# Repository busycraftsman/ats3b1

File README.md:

# ats3b1 project

# AT Sprint 3B.1
AT Sprint 3B1. 6 Bands HF CW/Digital Transceiver, designed by kd1jv.

# AT Sprint 3b.1 filter
filter board

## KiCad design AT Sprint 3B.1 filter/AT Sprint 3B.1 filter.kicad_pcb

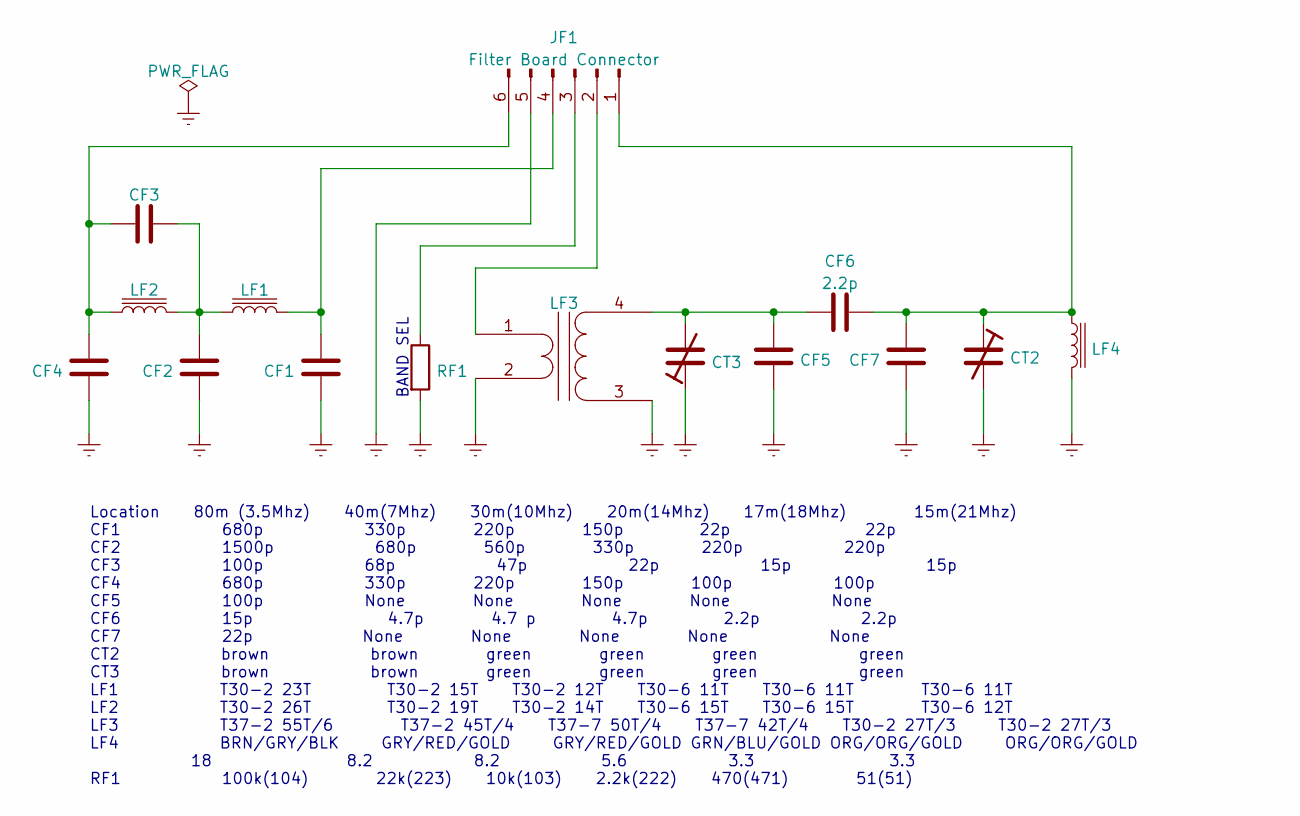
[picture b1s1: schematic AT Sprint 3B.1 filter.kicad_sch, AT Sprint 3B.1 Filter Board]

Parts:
CF1, CF2, CF3, CF4, CF5, CF7: C; C_Disc_D5.0mm_W2.5mm_P5.00mm
CF6: 2.2p; C_Disc_D5.0mm_W2.5mm_P5.00mm
CT2, CT3: C_Trim; C_TRIMMER_TZ03
JF1: Filter Board Connector; PinHeader_1x06_P2.54mm_Vertical
LF1, LF2: L_Iron; Toroid_horizontal_T37
LF3: Transformer_1P_1S_1vsN; Toroid_transformer_horizontal_T37
LF4: L_Iron; L_Axial_L7.0mm_D3.3mm_P2.54mm_Vertical_Fastron_MICC
RF1: R; R_0805_2012Metric_Pad1.20x1.40mm_HandSolder

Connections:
GNDREF: CF1.2, CF2.2, CF4.1, CF5.2, CF7.1, CT2.2, CT3.1, JF1.5, LF3.2 (AB), LF3.3 (SA), LF4.2, RF1.2
unnamed: CF1.1, JF1.4, LF1.2
unnamed: CF2.1, CF3.2, LF1.1, LF2.2
unnamed: CF3.1, CF4.2, JF1.6, LF2.1
unnamed: CF5.1, CF6.1, CT3.2, LF3.4 (SB)
unnamed: CF6.2, CF7.2, CT2.1, JF1.1, LF4.1
unnamed: JF1.2, LF3.1 (AA)
unnamed: JF1.3, RF1.1

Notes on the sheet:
BAND SEL
Location 80m (3.5Mhz) 40m(7Mhz) 30m(10Mhz) 20m(14Mhz) 17m(18Mhz) 15m(21Mhz) CF1 680p 330p 220p 150p 22p 22p CF2 1500p 680p 560p 330p 220p 220p CF3 100p 68p 47p 22p 15p 15p CF4 680p 330p 220p 150p 100p 100p CF5 100p None None None None None CF6 15p 4.7p 4.7 p 4.7p 2.2p 2.2p CF7 22p None None None No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

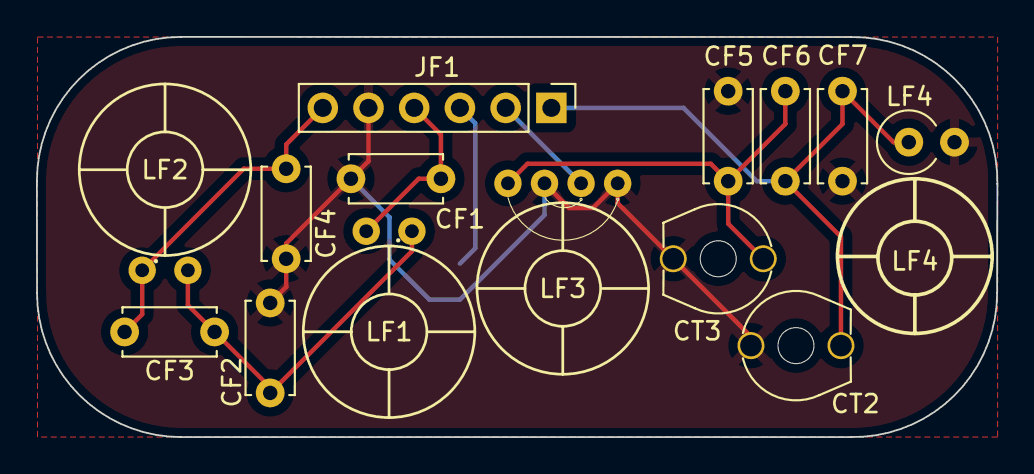
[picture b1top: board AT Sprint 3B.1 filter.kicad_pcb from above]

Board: 2 copper layers, 53.4 x 22.2 mm, 15 parts (1 on the bottom side), 8 nets.

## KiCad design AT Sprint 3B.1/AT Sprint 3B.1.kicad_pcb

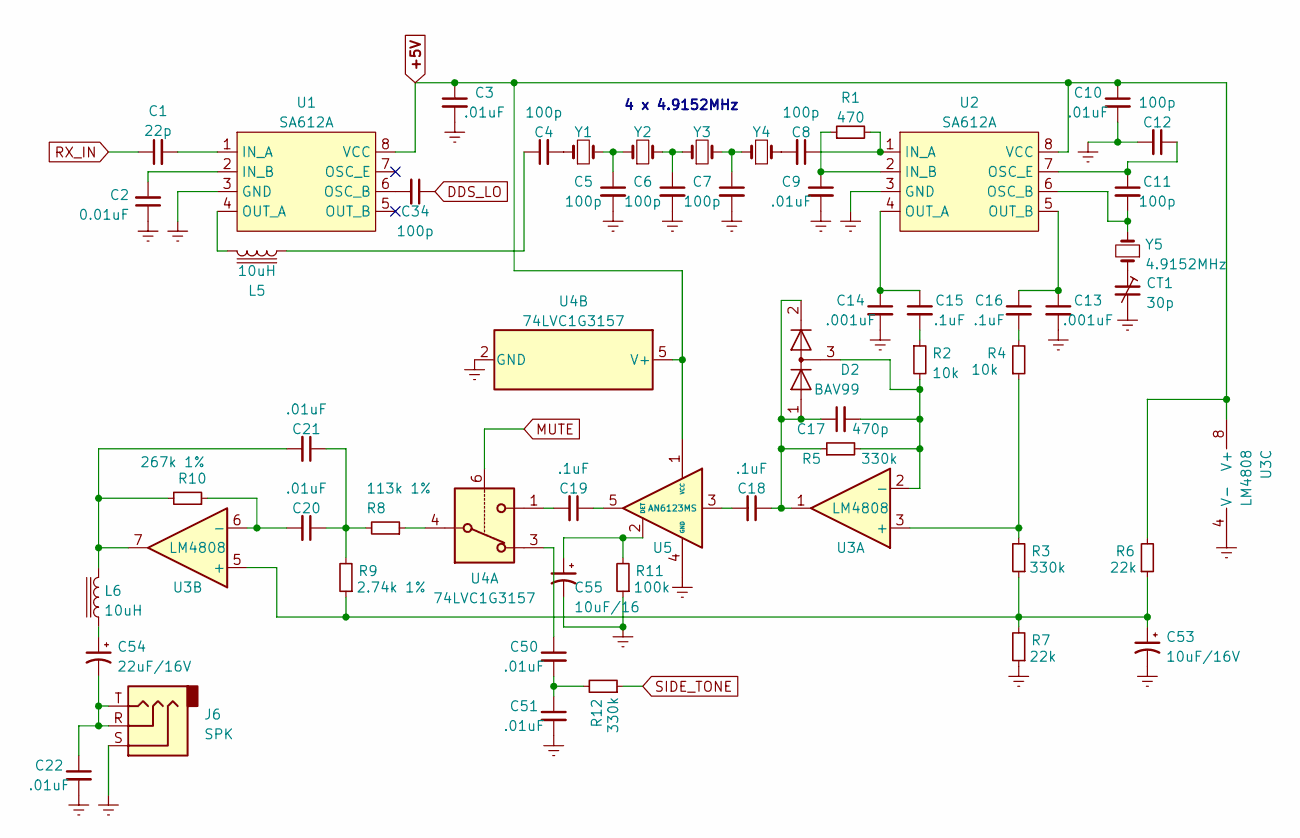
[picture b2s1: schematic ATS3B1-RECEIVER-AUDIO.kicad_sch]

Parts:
C1: 22p; C_0805_2012Metric
C2: 0.01uF; C_0805_2012Metric
C3, C9, C10, C20, C21, C22, C50, C51: .01uF; C_0805_2012Metric
C4, C5, C6, C7, C8, C11, C12, C34: 100p; C_0805_2012Metric
C13, C14: .001uF; C_0805_2012Metric
C15, C16, C18, C19: .1uF; C_0805_2012Metric
C17: 470p; C_0805_2012Metric
C53: 10uF/16V; CP_Radial_D5.0mm_P2.00mm
C54: 22uF/16V; CP_Radial_D5.0mm_P2.00mm
C55: 10uF/16; CP_Radial_D5.0mm_P2.00mm
CT1: 30p; C_TRIMMER_TZ03
D2: BAV99; SOT-23
J6: SPK; Jack_3.5mm_CUI_SJ-3523-SMT_Horizontal
L5, L6: 10uH; L_2010_5025Metric
R1: 470; R_0805_2012Metric
R2, R4: 10k; R_0805_2012Metric
R3, R5, R12: 330k; R_0805_2012Metric
R6, R7: 22k; R_0805_2012Metric
R8: 113k 1%; R_0805_2012Metric
R9: 2.74k 1%; R_0805_2012Metric
R10: 267k 1%; R_0805_2012Metric
R11: 100k; R_0805_2012Metric
U1, U2: SA612A; PowerIntegrations_SO-8
U3: LM4808; SOIC-8_3.9x4.9mm_P1.27mm
U4: 74LVC1G3157; SOT-666
U5: AN6123MS; SOT-553
Y1, Y2, Y3, Y4, Y5: 4.9152MHz; HC49US

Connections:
+5V: C3.1, C10.1, R6.2, U1.8 (VCC), U2.8 (VCC), U3.8 (V+), U4.5 (V+), U5.1 (VCC); also elsewhere on the board
DDS_LO: C34.1; also elsewhere on the board
GNDREF: C2.1, C3.2, C5.2, C6.2, C7.2, C9.2, C10.2, C12.2, C13.2, C14.2, C22.2, C51.2, C53.2, C55.2, CT1.2, J6.S, R7.1, R11.1, U1.3 (GND), U2.3 (GND), U3.4 (V-), U4.2 (GND), U5.4 (GND); also elsewhere on the board
unnamed: C1.2, U1.1 (IN_A)
unnamed: C2.2, U1.2 (IN_B)
unnamed: C4.1, L5.1
unnamed: C4.2, Y1.1
unnamed: C5.1, Y1.2, Y2.1
unnamed: C6.1, Y2.2, Y3.1
unnamed: C7.1, Y3.2, Y4.1
unnamed: C8.1, R1.2, U2.1 (IN_A)
unnamed: C8.2, Y4.2
unnamed: C9.1, R1.1, U2.2 (IN_B)
unnamed: C11.1, C12.1, U2.7 (OSC_E)
unnamed: C11.2, U2.6 (OSC_B), Y5.2
unnamed: C13.1, C16.1, U2.5 (OUT_B)
unnamed: C14.1, C15.1, U2.4 (OUT_A)
unnamed: C15.2, R2.1
unnamed: C16.2, R4.2
unnamed: C17.1, C18.1, D2.1 (K), D2.2 (A), R5.1, U3.1
unnamed: C17.2, D2.3 (K), R2.2, R5.2, U3.2 (-)
unnamed: C18.2, U5.3
unnamed: C19.1, U5.5
unnamed: C19.2, U4.1
unnamed: C20.1, C21.1, R8.2, R9.2
unnamed: C20.2, R10.1, U3.6 (-)
unnamed: C21.2, L6.2, R10.2, U3.7
unnamed: C22.1, C54.2, J6.R, J6.T
unnamed: C34.2, U1.6 (OSC_B)
unnamed: C50.1, U4.3
unnamed: C50.2, C51.1, R12.2
unnamed: C53.1, R3.1, R6.1, R7.2, R9.1, U3.5 (+)
unnamed: C54.1, L6.1
unnamed: C55.1, R11.2, U5.2 (DET)
unnamed: CT1.1, Y5.1
unnamed: L5.2, U1.4 (OUT_A)
unnamed: R3.2, R4.1, U3.3 (+)
unnamed: R8.1, U4.4
RX_IN: C1.1; also elsewhere on the board
SIDE_TONE: R12.1; also elsewhere on the board

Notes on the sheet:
4 x 4.9152MHz

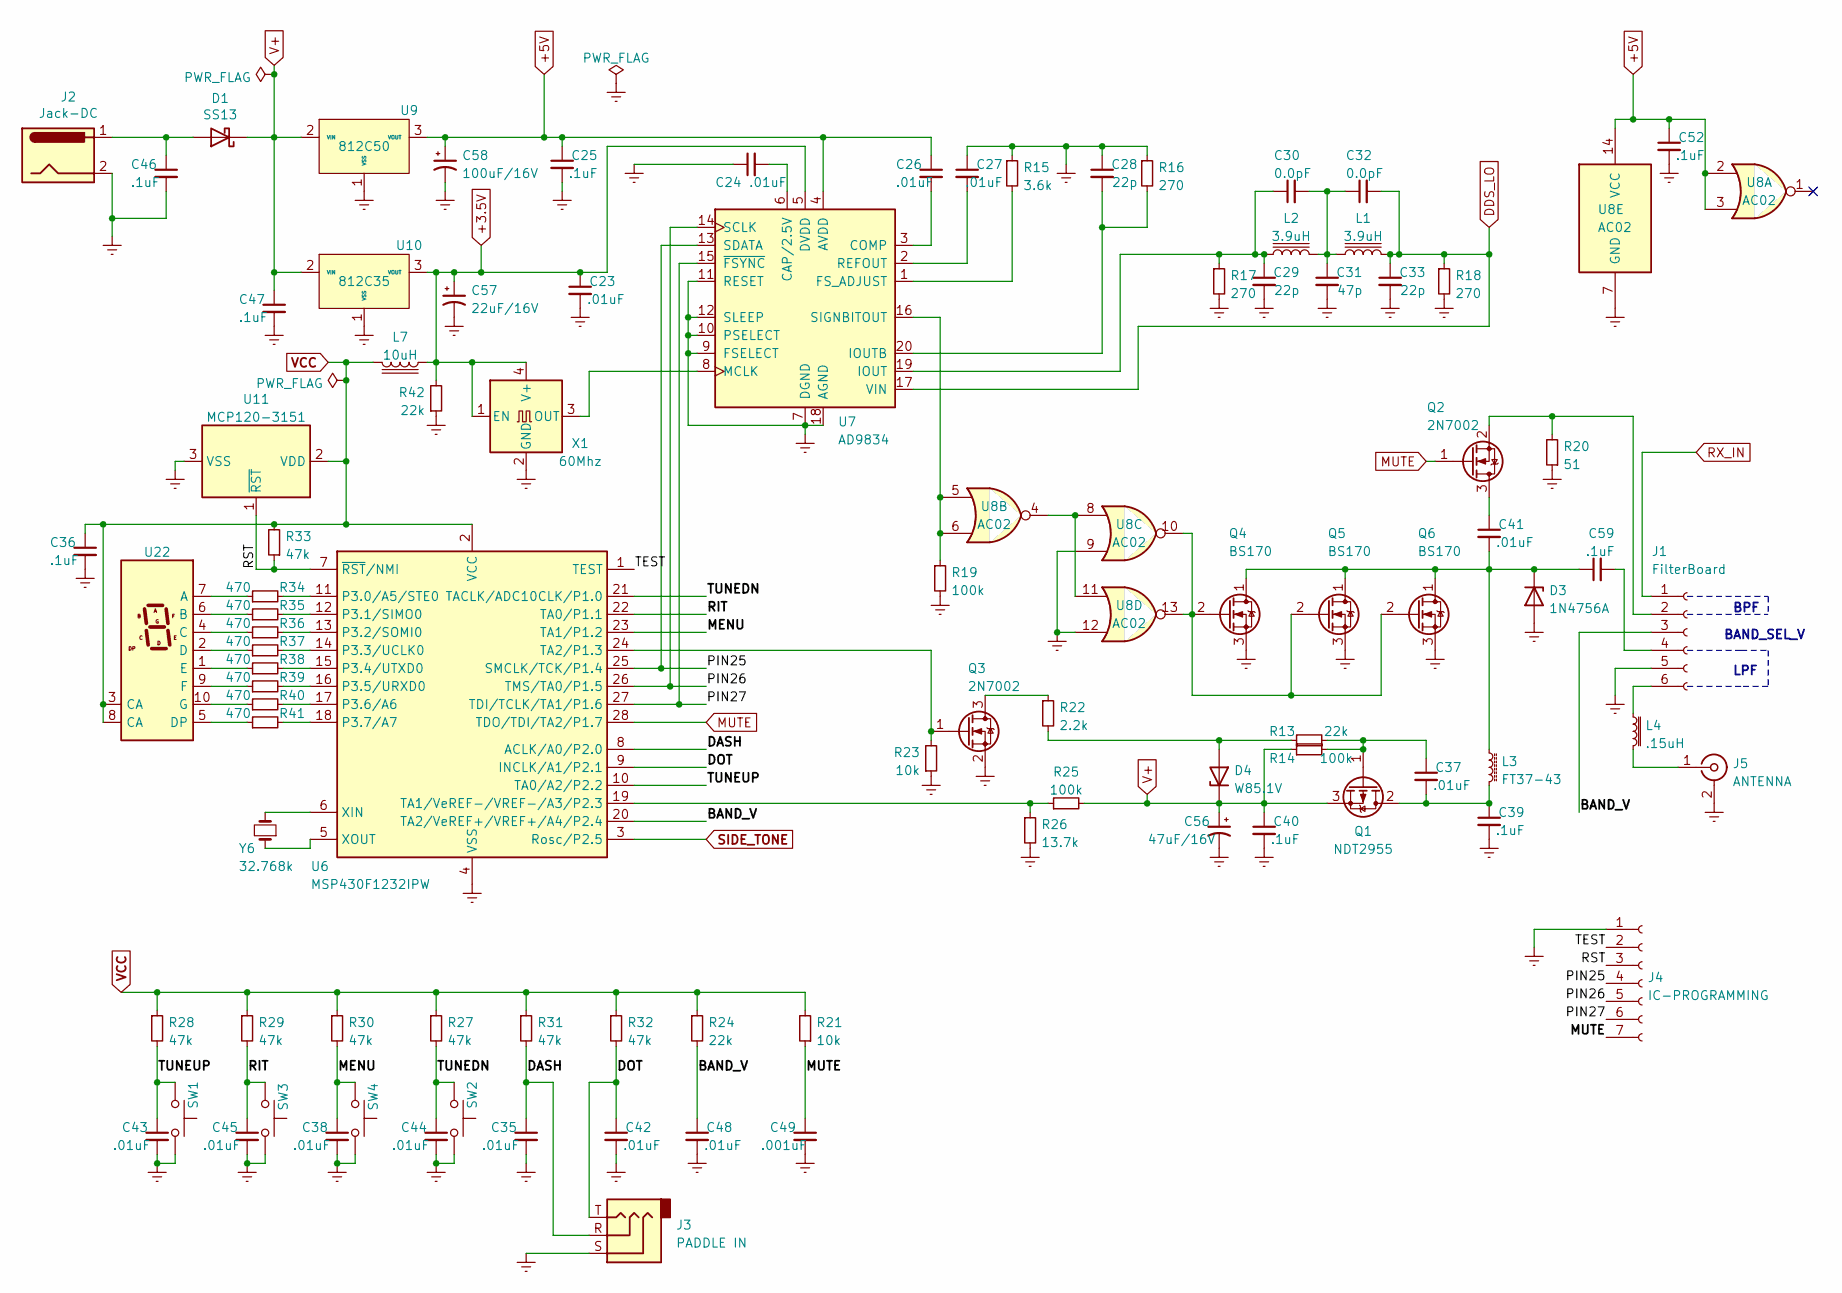
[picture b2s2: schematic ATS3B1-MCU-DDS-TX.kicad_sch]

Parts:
C23, C24, C26, C27, C35, C37, C38, C41, C42, C43, C44, C45, C48: .01uF; C_0805_2012Metric
C25, C36, C39, C40, C46, C47, C52: .1uF; C_0805_2012Metric
C28, C29, C33: 22p; C_0805_2012Metric
C30, C32: 0.0pF; C_0805_2012Metric
C31: 47p; C_0805_2012Metric
C49: .001uF; C_0805_2012Metric
C56: 47uF/16V; CP_Radial_D5.0mm_P2.00mm
C57: 22uF/16V; CP_Radial_D5.0mm_P2.00mm
C58: 100uF/16V; CP_Radial_D5.0mm_P2.00mm
C59: .1uF; C_Disc_D3.8mm_W2.6mm_P2.50mm
D1: SS13; D_SMA
D3: 1N4756A; D_DO-41_SOD81_P7.62mm_Horizontal
D4: W85.1V; D_SOD-123
J1: FilterBoard; PinSocket_1x06_P2.54mm_Vertical
J2: Jack-DC; CUI_PJ-041-SMT-TR
J3: PADDLE IN; Jack_3.5mm_CUI_SJ-3523-SMT_Horizontal
J4: IC-PROGRAMMING; PinHeader_1x07_P2.54mm_Vertical
J5: ANTENNA; PinHeader_1x02_P2.54mm_Vertical
L1, L2: 3.9uH; L_2010_5025Metric
L3: FT37-43; Choke_Toroid_horizontal_Diameter10-5mm_Amidon-FT37
L4: .15uH; L_2010_5025Metric
L7: 10uH; L_2010_5025Metric
Q1: NDT2955; Trans_SOT-223-4
Q2, Q3: 2N7002; SOT-23
Q4, Q5, Q6: BS170; TO-92
R13, R24, R42: 22k; R_0805_2012Metric
R14, R19, R25: 100k; R_0805_2012Metric
R15: 3.6k; R_0805_2012Metric
R16, R17, R18: 270; R_0805_2012Metric
R20: 51; R_0805_2012Metric
R21, R23: 10k; R_0805_2012Metric
R22: 2.2k; R_0805_2012Metric
R26: 13.7k; R_0805_2012Metric
R27, R28, R29, R30, R31, R32, R33: 47k; R_0805_2012Metric
R34, R35, R36, R37, R38, R39, R40, R41: 470; R_0805_2012Metric
SW1, SW2, SW3, SW4: SW_Push; SW_PUSH_6mm
U6: MSP430F1232IPW; TSSOP-28_4.4x9.7mm_P0.65mm
U7: AD9834; TSSOP-20_4.4x6.5mm_P0.65mm
U8: AC02; SSOP-14_5.3x6.2mm_P0.65mm
U9: 812C50; SOT-89-3
U10: 812C35; SOT-89-3
U11: MCP120-3151; SOT-23
U22: KCSA02-107; KCSC02-105
X1: 60Mhz; Oscillator_SMD_EuroQuartz_XO91-4Pin_7.0x5.0mm_HandSoldering
Y6: 32.768k; CRYSTAL-PTH-2X6-CYL

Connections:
+3.5V: C23.1, C57.1, L7.1, R42.2, U7.5 (DVDD), U10.3 (VOUT), X1.1 (EN), X1.4 (V+)
+5V: C25.1, C26.1, C52.1, C58.1, U7.4 (AVDD), U8.2, U8.3, U8.14 (VCC), U9.3 (VOUT); also elsewhere on the board
/ATS3B1-MCU-DDS-TX/BAND_V: C48.1, J1.3, R24.2, U6.20 (TA2/VeREF+/VREF+/A4/P2.4)
/ATS3B1-MCU-DDS-TX/DASH: C35.1, J3.R, R31.2, U6.8 (ACLK/A0/P2.0)
/ATS3B1-MCU-DDS-TX/DOT: C42.1, J3.T, R32.2, U6.9 (INCLK/A1/P2.1)
/ATS3B1-MCU-DDS-TX/MENU: C38.1, R30.2, SW4.2, U6.23 (TA1/P1.2)
/ATS3B1-MCU-DDS-TX/PIN25: J4.4, U6.25 (SMCLK/TCK/P1.4), U7.13 (SDATA)
/ATS3B1-MCU-DDS-TX/PIN26: J4.5, U6.26 (TMS/TA0/P1.5), U7.14 (SCLK)
/ATS3B1-MCU-DDS-TX/PIN27: J4.6, U6.27 (TDI/TCLK/TA1/P1.6), U7.15 (~FSYNC)
/ATS3B1-MCU-DDS-TX/RIT: C45.1, R29.2, SW3.2, U6.22 (TA0/P1.1)
/ATS3B1-MCU-DDS-TX/RST: J4.3, R33.1, U6.7 (~RST/NMI), U11.1 (~RST)
/ATS3B1-MCU-DDS-TX/TEST: J4.2, U6.1 (TEST)
/ATS3B1-MCU-DDS-TX/TUNEDN: C44.1, R27.2, SW2.2, U6.21 (TACLK/ADC10CLK/P1.0)
/ATS3B1-MCU-DDS-TX/TUNEUP: C43.1, R28.2, SW1.2, U6.10 (TA0/A2/P2.2)
DDS_LO: C32.2, C33.1, L1.2, R18.1, U7.17 (VIN); also elsewhere on the board
GNDREF: C23.2, C24.1, C25.2, C27.1, C28.1, C29.2, C31.2, C33.2, C35.2, C36.2, C38.2, C39.2, C40.2, C42.2, C43.2, C44.2, C45.2, C46.2, C47.2, C48.2, C49.2, C52.2, C56.2, C57.2, C58.2, D3.2 (A), J1.5, J2.2, J3.S, J4.1, J5.2 (Ext), Q3.2 (S), Q4.3 (S), Q5.3 (S), Q6.3 (S), R15.1, R16.1, R17.2, R18.2, R19.2, R20.1, R23.1, R26.2, R42.1, SW1.1, SW2.1, SW3.1, SW4.1, U6.4 (VSS), U7.7 (DGND), U7.9 (FSELECT), U7.10 (PSELECT), U7.11 (RESET), U7.12 (SLEEP), U7.18 (AGND), U8.7 (GND), U8.9, U8.12, U9.1 (VSS), U10.1 (VSS), U11.3 (VSS), X1.2 (GND); also elsewhere on the board
unnamed: C24.2, U7.6 (CAP/2.5V)
unnamed: C26.2, U7.3 (COMP)
unnamed: C27.2, U7.2 (REFOUT)
unnamed: C28.2, R16.2, U7.20 (IOUTB)
unnamed: C29.1, C30.1, L2.1, R17.1, U7.19 (IOUT)
unnamed: C30.2, C31.1, C32.1, L1.1, L2.2
unnamed: C37.1, Q1.1 (G), R13.2, R14.2
unnamed: C37.2, C39.1, L3.2, Q1.2 (D)
unnamed: C41.1, Q2.3 (D)
unnamed: C41.2, C59.1, D3.1 (K), L3.1, Q4.1 (D), Q5.1 (D), Q6.1 (D)
unnamed: C46.1, D1.2 (A), J2.1
unnamed: C59.2, J1.4
unnamed: D4.2 (A), R13.1, R22.2
unnamed: J1.2, Q2.2 (S), R20.2
unnamed: J1.6, L4.1
unnamed: J5.1 (In), L4.2
unnamed: Q3.1 (G), R23.2, U6.24 (TA2/P1.3)
unnamed: Q3.3 (D), R22.1
unnamed: Q4.2 (G), Q5.2 (G), Q6.2 (G), U8.10, U8.13
unnamed: R15.2, U7.1 (FS_ADJUST)
unnamed: R19.1, U7.16 (SIGNBITOUT), U8.5, U8.6
unnamed: R25.1, R26.1, U6.19 (TA1/VeREF-/VREF-/A3/P2.3)
unnamed: R34.1, U22.7 (A)
unnamed: R34.2, U6.11 (P3.0/A5/STE0)
unnamed: R35.1, U22.6 (B)
unnamed: R35.2, U6.12 (P3.1/SIMO0)
unnamed: R36.1, U22.4 (C)
unnamed: R36.2, U6.13 (P3.2/SOMI0)
unnamed: R37.1, U22.2 (D)
unnamed: R37.2, U6.14 (P3.3/UCLK0)
unnamed: R38.1, U22.1 (E)
unnamed: R38.2, U6.15 (P3.4/UTXD0)
unnamed: R39.1, U22.9 (F)
unnamed: R39.2, U6.16 (P3.5/URXD0)
unnamed: R40.1, U22.10 (G)
unnamed: R40.2, U6.17 (P3.6/A6)
unnamed: R41.1, U22.5 (DP)
unnamed: R41.2, U6.18 (P3.7/A7)
unnamed: U6.5 (XOUT), Y6.1
unnamed: U6.6 (XIN), Y6.2
unnamed: U7.8 (MCLK), X1.3 (OUT)
unnamed: U8.4, U8.8, U8.11
RX_IN: J1.1; also elsewhere on the board
SIDE_TONE: U6.3 (Rosc/P2.5); also elsewhere on the board
V+: C40.1, C47.1, C56.1, D1.1 (K), D4.1 (K), Q1.3 (S), R14.1, R25.2, U9.2 (VIN), U10.2 (VIN)

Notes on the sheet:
BAND_SEL_V
LPF
BPF

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
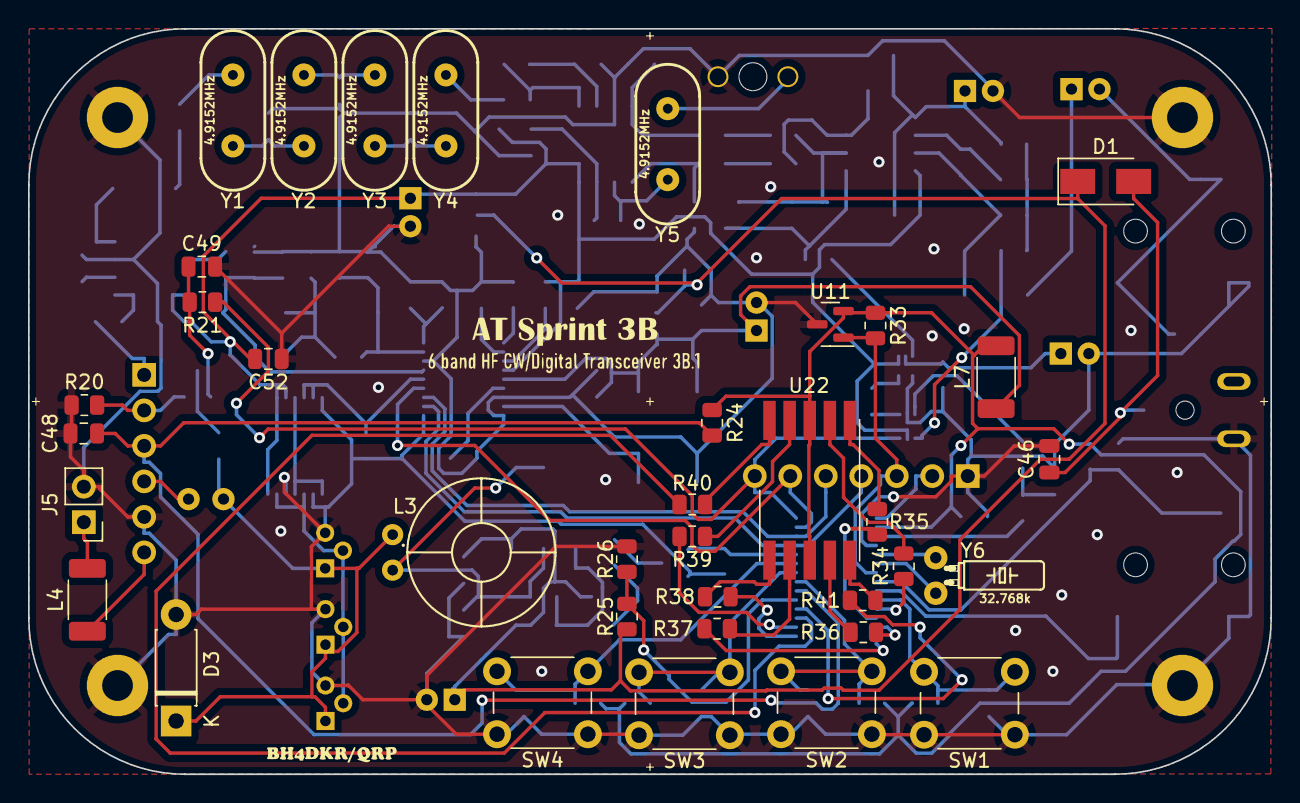
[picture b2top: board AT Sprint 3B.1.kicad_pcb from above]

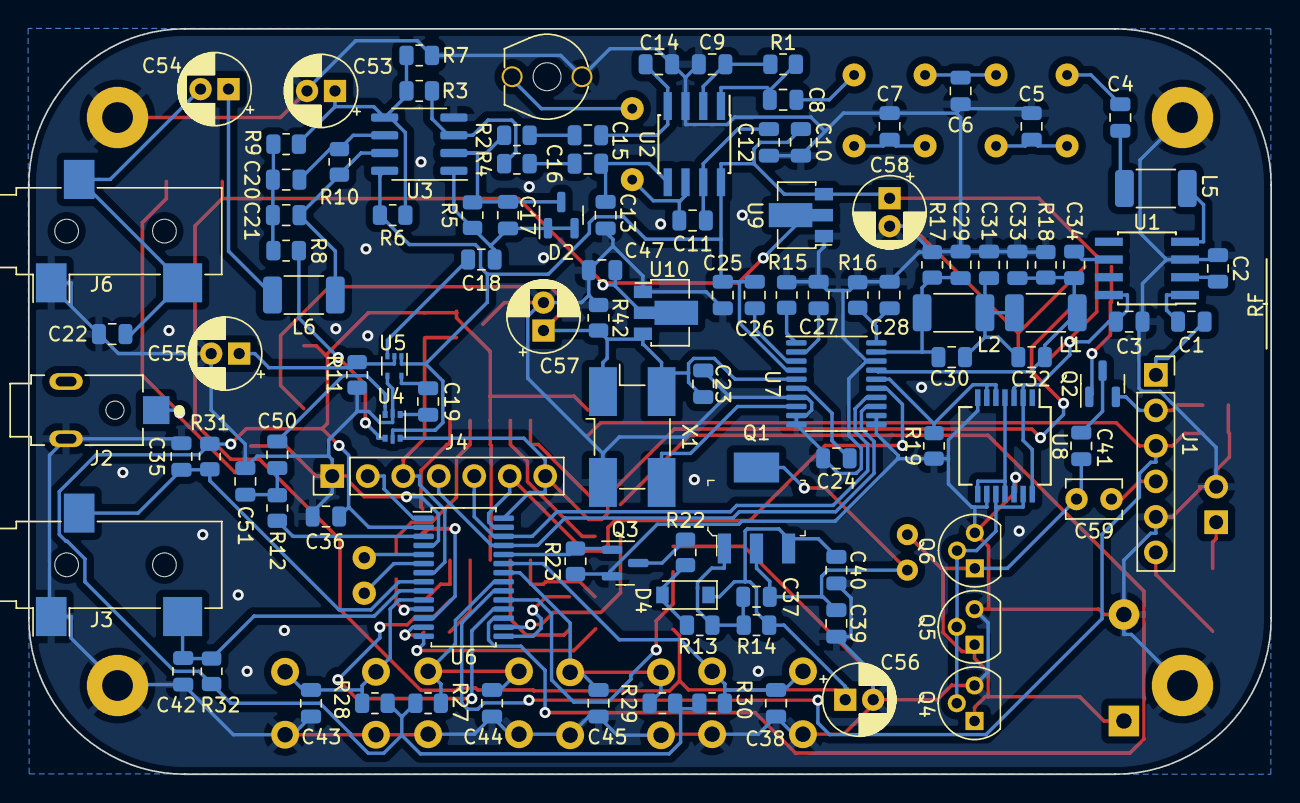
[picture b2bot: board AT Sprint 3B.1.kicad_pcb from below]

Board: 2 copper layers, 88.9 x 53.3 mm, 148 parts (112 on the bottom side), 99 nets.

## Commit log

2022-05-20 add first version
2022-05-20 remove freeroute interchange files
2022-05-20 update message
2022-05-21 add filter boundary in User.Drawing layer, fit room for filter board
2022-05-21 generate ats3b1 filter gerb file
2022-05-21 change text size for production
2022-05-21 fix C11 footprint
2022-05-21 fix C22 TRS connection error
2022-05-23 fix some errors. release for pcb production
